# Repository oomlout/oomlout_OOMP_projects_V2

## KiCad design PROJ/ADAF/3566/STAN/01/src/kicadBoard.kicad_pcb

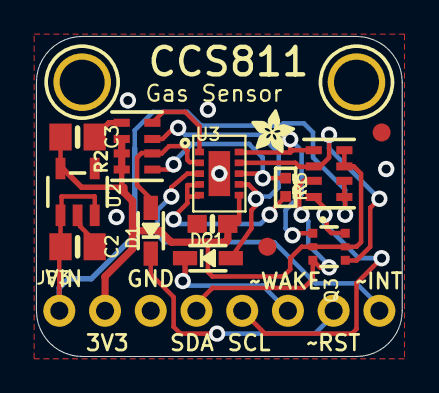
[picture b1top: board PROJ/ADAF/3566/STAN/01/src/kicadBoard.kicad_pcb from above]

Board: 2 copper layers, 20.3 x 17.8 mm, 18 parts (1 on the bottom side), 15 nets.

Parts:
C1: 0.1uF; 0603-NO
C2, C3: 10uF; 0805-NO
D1, D2: 1N4148; SOD-323
FID1, FID2: FIDUCIAL_1MM
JP3: 1X08_ROUND_70
Q3: 2N7002D; SOT363
R1: 10k; RESPACK_4X0603
R2: 100k; RESPACK_4X0603
R5: 10K NTC; _0402
U2: MIC5225-3.3; SOT23-5
U3: CCS811
U$1: ADAFRUIT_3.5MM
U$3, U$4: MOUNTINGHOLE2.5; MOUNTINGHOLE_2.5_PLATED
U$8: ADAFRUIT_2.5MM

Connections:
3.3V: C1.1, C3.1, JP3.2, Q3.2, Q3.5, R1.3, R1.4, R2.6, R2.7, R2.8, U2.5, U3.6
GND: C1.2, C2.2, C3.2, JP3.3, R2.5, U2.2, U3.THERMAL
unnamed: R5.2, U3.4, U3.5
unnamed: R2.1, R5.1, U3.8
unnamed: R2.4, U3.1
SCL: JP3.5, Q3.6, R1.8
SCL_3V: Q3.1, R1.5, U3.10
SDA: JP3.4, Q3.3, R1.7
SDA_3V: Q3.4, R1.6, U3.9
VIN: C2.1, JP3.1, R1.1, R1.2, U2.1, U2.3
~INT: JP3.8, U3.3
~RESET: D1.C, JP3.7
~RST_3V: D1.A, R2.2, U3.2
~WAKE_3V: D2.A, R2.3, U3.7
~WAKE: D2.C, JP3.6

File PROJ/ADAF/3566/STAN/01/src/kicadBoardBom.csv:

"Id";"Designator";"Package";"Quantity";"Designation";"Supplier and ref";
1;"Q3";"SOT363";1;"2N7002D";;;
2;"U$4,U$3";"MOUNTINGHOLE_2.5_PLATED";2;"MOUNTINGHOLE2.5";;;
3;"D1,D2";"SOD-323";2;"1N4148";;;
4;"C3,C2";"0805-NO";2;"10uF";;;
5;"R1";"RESPACK_4X0603";1;"10k";;;
6;"U2";"SOT23-5";1;"MIC5225-3.3";;;
7;"FID1,FID2";"FIDUCIAL_1MM";2;"FIDUCIAL_1MM";;;
8;"C1";"0603-NO";1;"0.1uF";;;
9;"R2";"RESPACK_4X0603";1;"100k";;;
10;"R5";"_0402";1;"10K NTC";;;
11;"U$8";"ADAFRUIT_2.5MM";1;"";;;
12;"JP3";"1X08_ROUND_70";1;"";;;
13;"U3";"CCS811";1;"CCS811";;;
14;"U$1";"ADAFRUIT_3.5MM";1;"";;;

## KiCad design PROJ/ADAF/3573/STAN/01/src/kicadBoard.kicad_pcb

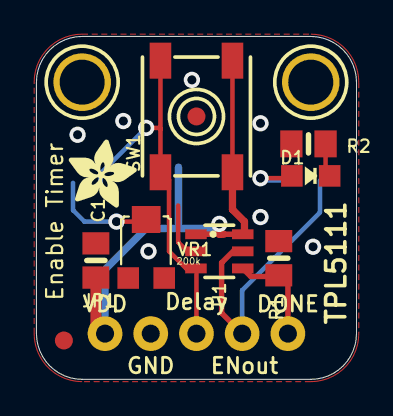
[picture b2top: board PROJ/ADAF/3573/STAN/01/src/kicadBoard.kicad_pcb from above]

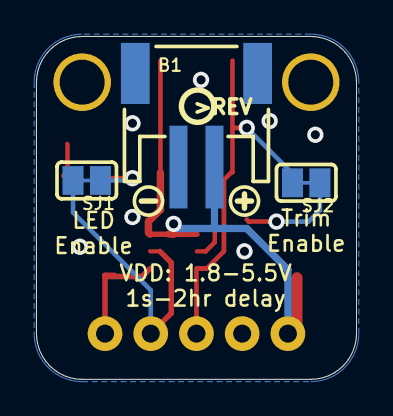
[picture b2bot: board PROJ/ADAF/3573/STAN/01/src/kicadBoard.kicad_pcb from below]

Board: 2 copper layers, 17.8 x 19.0 mm, 19 parts (6 on the bottom side), 8 nets.

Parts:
B1: JSTPH2
C1: 10uF; 0805-NO
D1: GREEN; CHIPLED_0805_NOOUTLINE
FID2, FID3: FIDUCIAL_1MM
JP1: 1X05_ROUND_76
R1: 1M; 0805-NO
R2: 1K; 0805-NO
SJ1, SJ2: SOLDERJUMPER_CLOSEDWIRE
SW1: MANUAL; EVQ-Q2_SMALLER
U1: TPL5111DDC; SOT23-6
U$8, U$9: MOUNTINGHOLE2.5; MOUNTINGHOLE_2.5_PLATED
U$10: ADAFRUIT_3.5MM
U$11: SYMBOL_PLUS
U$12: SYMBOL_MINUS
U$15: PCBFEAT-REV-040
VR1: 200k; TRIMPOT_BOURNS_TC33X-2

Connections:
DELAY: JP1.3, SJ2.2, SW1.B, SW1.B', U1.3
DONE: JP1.5, R1.2, U1.4
ENOUT: JP1.4, SJ1.2, U1.5
GND: B1.1, C1.2, JP1.2, R1.1, R2.1, U1.2, VR1.3
unnamed: SJ2.1, VR1.2
unnamed: D1.A, SJ1.1
unnamed: D1.C, R2.2
VDD: B1.2, C1.1, JP1.1, SW1.A, SW1.A', U1.1, U1.6

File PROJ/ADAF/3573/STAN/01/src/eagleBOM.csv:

"Part";"Value";"Device";"Package";"Description";"BOM";
"B1";"JSTPH2";"BATTERY";"JSTPH2";"CR1220 SMT - Digikey: 3001K-ND";"";
"C1";"10uF";"CAP_CERAMIC0805-NOOUTLINE";"0805-NO";"Ceramic Capacitors";"";
"D1";"GREEN";"LED0805_NOOUTLINE";"CHIPLED_0805_NOOUTLINE";"LED";"";
"FID2";"FIDUCIAL_1MM";"FIDUCIAL_1MM";"FIDUCIAL_1MM";"Fiducial Alignment Points";"EXCLUDE";
"FID3";"FIDUCIAL_1MM";"FIDUCIAL_1MM";"FIDUCIAL_1MM";"Fiducial Alignment Points";"EXCLUDE";
"JP1";"";"HEADER-1X576MIL";"1X05_ROUND_76";"PIN HEADER";"";
"R1";"1M";"RESISTOR0805_NOOUTLINE";"0805-NO";"Resistors";"";
"R2";"1K";"RESISTOR0805_NOOUTLINE";"0805-NO";"Resistors";"";
"SJ1";"";"SOLDERJUMPERCLOSED";"SOLDERJUMPER_CLOSEDWIRE";"SMD Solder JUMPER";"";
"SJ2";"";"SOLDERJUMPERCLOSED";"SOLDERJUMPER_CLOSEDWIRE";"SMD Solder JUMPER";"";
"SW1";"MANUAL";"SWITCH_TACT_SMT_EVQQ2_SMALL";"EVQ-Q2_SMALLER";"SMT Tact Switches";"";
"U$8";"MOUNTINGHOLE2.5";"MOUNTINGHOLE2.5";"MOUNTINGHOLE_2.5_PLATED";"Mounting Hole";"EXCLUDE";
"U$9";"MOUNTINGHOLE2.5";"MOUNTINGHOLE2.5";"MOUNTINGHOLE_2.5_PLATED";"Mounting Hole";"EXCLUDE";
"U1";"TPL5111DDC";"TPL5111";"SOT23-6";"TPL5111 Timer Based Power Gate";"";
"VR1";"200k";"TRIMPOTTC33X-2";"TRIMPOT_BOURNS_TC33X-2";"3-Pin SMT Trimpots";"";

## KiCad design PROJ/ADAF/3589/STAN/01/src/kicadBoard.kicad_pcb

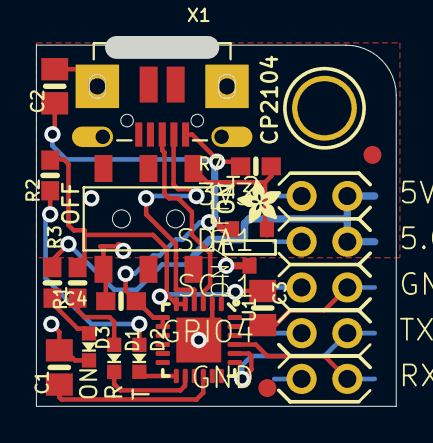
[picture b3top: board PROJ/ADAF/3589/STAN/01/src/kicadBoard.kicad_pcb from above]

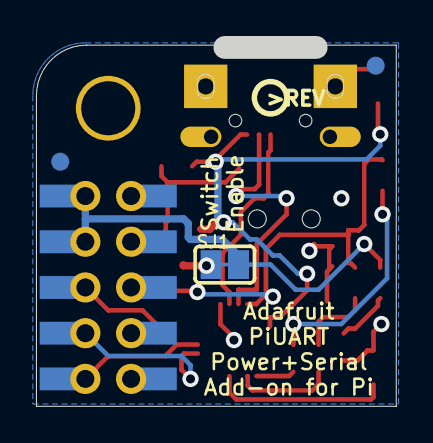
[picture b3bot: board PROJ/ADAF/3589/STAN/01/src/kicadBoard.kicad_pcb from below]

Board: 2 copper layers, 20.0 x 20.1 mm, 24 parts (4 on the bottom side), 20 nets.

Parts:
C1, C2, C3: 10uF; 0805-NO
C4: 0.1uF; 0603-NO
D1: RED; CHIPLED_0603_NOOUTLINE
D2: YELLOW; CHIPLED_0603_NOOUTLINE
D3: GREEN; CHIPLED_0603_NOOUTLINE
FID1, FID2, FID3, FID4: FIDUCIAL_1MM
ON/OFF0: EG1390
R1, R2: 2.2K; 0603-NO
R3, R7: 10K; 0603-NO
SJ1: SOLDERJUMPER_CLOSEDWIRE
T2: DMG3415U; SOT-23
U1: CP2104; QFN24_4MM_SMSC
U$8: ADAFRUIT_2.5MM
U$9: RASPBERRYPI_2X5; RASPBERRYPI_2X5_THMSMT
U$17: PCBFEAT-REV-040
U$18: MOUNTINGHOLE3.0THIN; MOUNTINGHOLE_3.0_PLATEDTHIN
X1: 20329; 4UCONN_20329_V2

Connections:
3.3V: C3.1, R1.2, R2.2, U1.5, U1.6
GND: C1.2, C2.2, C3.2, C4.2, D3.C, ON/OFF0.P2, ON/OFF0.S1, U1.2, U1.THERM, U$9.6, U$9.6', U$9.9, U$9.9', X1.BASE@1, X1.BASE@2, X1.GND, X1.SPRT@1, X1.SPRT@2, X1.SPRT@3, X1.SPRT@4
unnamed: D1.A, R1.1
unnamed: U1.3, X1.D+
unnamed: U1.4, X1.D-
unnamed: C1.1, U1.16
unnamed: D2.A, R2.1
unnamed: D1.C, U1.14
unnamed: D2.C, U1.13
unnamed: U$9.1, U$9.1'
unnamed: U$9.3, U$9.3'
unnamed: U$9.7, U$9.7'
unnamed: U$9.5, U$9.5'
unnamed: R3.2, SJ1.2, U$9.2, U$9.2', U$9.4, U$9.4'
unnamed: ON/OFF0.O2, R7.1, T2.3
unnamed: D3.A, R3.1
RXD: U1.21, U$9.10, U$9.10'
TXD: U1.20, U$9.8, U$9.8'
VBUS: C2.1, C4.1, R7.2, T2.2, U1.7, U1.8, X1.VBUS
VIN: SJ1.1, T2.1

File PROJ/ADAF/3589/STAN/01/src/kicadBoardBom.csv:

"Id";"Designator";"Package";"Quantity";"Designation";"Supplier and ref";
1;"U1";"QFN24_4MM_SMSC";1;"CP2104";;;
2;"FID2,FID1,FID3,FID4";"FIDUCIAL_1MM";4;"FIDUCIAL_1MM";;;
3;"R7,R3";"0603-NO";2;"10K";;;
4;"D3";"CHIPLED_0603_NOOUTLINE";1;"GREEN";;;
5;"C4";"0603-NO";1;"0.1uF";;;
6;"U$18";"MOUNTINGHOLE_3.0_PLATEDTHIN";1;"MOUNTINGHOLE3.0THIN";;;
7;"U$9";"RASPBERRYPI_2X5_THMSMT";1;"RASPBERRYPI_2X5";;;
8;"C1,C3,C2";"0805-NO";3;"10uF";;;
9;"ON/OFF0";"EG1390";1;"EG1390";;;
10;"X1";"4UCONN_20329_V2";1;"20329";;;
11;"R1,R2";"0603-NO";2;"2.2K";;;
12;"D2";"CHIPLED_0603_NOOUTLINE";1;"YELLOW";;;
13;"D1";"CHIPLED_0603_NOOUTLINE";1;"RED";;;
14;"U$8";"ADAFRUIT_2.5MM";1;"";;;
15;"T2";"SOT-23";1;"DMG3415U";;;
16;"SJ1";"SOLDERJUMPER_CLOSEDWIRE";1;"";;;
17;"U$17";"PCBFEAT-REV-040";1;"";;;

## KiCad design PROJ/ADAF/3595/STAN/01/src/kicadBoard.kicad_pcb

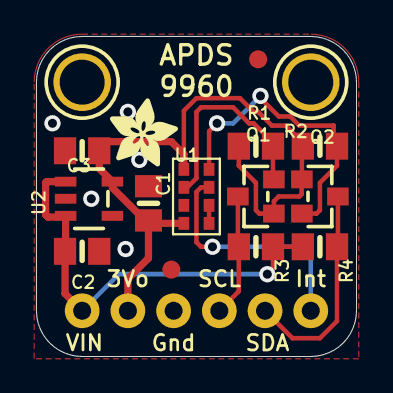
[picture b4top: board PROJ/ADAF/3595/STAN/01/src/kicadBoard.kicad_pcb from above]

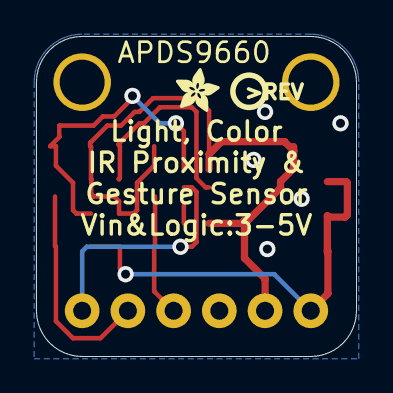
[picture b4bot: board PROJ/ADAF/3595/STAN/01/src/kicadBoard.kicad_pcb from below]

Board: 2 copper layers, 17.8 x 17.8 mm, 19 parts (2 on the bottom side), 9 nets.

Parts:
C1: 0.1uF; 0805-NO
C2, C3: 10uF; 0805-NO
FID1, FID2: FIDUCIAL_1MM
JP1: 1X06_ROUND_76
Q1, Q2: BSS138; SOT23-WIDE
R1, R2, R3, R4: 10K; 0805-NO
U1: APDS-9960
U2: SOT23-5
U$1, U$2: MOUNTINGHOLE2.5; MOUNTINGHOLE_2.5_PLATED
U$17: PCBFEAT-REV-040
U$18: ADAFRUIT_2.5MM
U$19: ADAFRUIT_3.5MM

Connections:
3.3V: C1.1, C3.1, JP1.2, Q1.1, Q2.1, R1.2, R2.2, U1.5, U1.8, U2.5
GND: C1.2, C2.2, C3.2, JP1.3, U1.6, U2.2
INT: JP1.6, U1.2
unnamed: U1.3, U1.4
SCL: JP1.4, Q1.3, R3.1
SCL_3V: Q1.2, R1.1, U1.7
SDA: JP1.5, Q2.3, R4.1
SDA_3V: Q2.2, R2.1, U1.1
VIN: C2.1, JP1.1, R3.2, R4.2, U2.1, U2.3

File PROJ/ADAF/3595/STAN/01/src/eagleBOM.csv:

"Part";"Value";"Device";"Package";"Description";"BOM";
"C1";"0.1uF";"CAP_CERAMIC0805-NOOUTLINE";"0805-NO";"Ceramic Capacitors";"";
"C2";"10uF";"CAP_CERAMIC0805-NOOUTLINE";"0805-NO";"Ceramic Capacitors";"";
"C3";"10uF";"CAP_CERAMIC0805-NOOUTLINE";"0805-NO";"Ceramic Capacitors";"";
"FID1";"FIDUCIAL_1MM";"FIDUCIAL_1MM";"FIDUCIAL_1MM";"Fiducial Alignment Points";"EXCLUDE";
"FID2";"FIDUCIAL_1MM";"FIDUCIAL_1MM";"FIDUCIAL_1MM";"Fiducial Alignment Points";"EXCLUDE";
"JP1";"";"HEADER-1X676MIL";"1X06_ROUND_76";"PIN HEADER";"";
"Q1";"BSS138";"MOSFET-NWIDE";"SOT23-WIDE";"N-Channel Mosfet";"";
"Q2";"BSS138";"MOSFET-NWIDE";"SOT23-WIDE";"N-Channel Mosfet";"";
"R1";"10K";"RESISTOR0805_NOOUTLINE";"0805-NO";"Resistors";"";
"R2";"10K";"RESISTOR0805_NOOUTLINE";"0805-NO";"Resistors";"";
"R3";"10K";"RESISTOR0805_NOOUTLINE";"0805-NO";"Resistors";"";
"R4";"10K";"RESISTOR0805_NOOUTLINE";"0805-NO";"Resistors";"";
"U$1";"MOUNTINGHOLE2.5";"MOUNTINGHOLE2.5";"MOUNTINGHOLE_2.5_PLATED";"Mounting Hole";"EXCLUDE";
"U$2";"MOUNTINGHOLE2.5";"MOUNTINGHOLE2.5";"MOUNTINGHOLE_2.5_PLATED";"Mounting Hole";"EXCLUDE";
"U1";"APDS-9960";"APDS-9960";"APDS-9960";"APDS-9960 - Digital Proximity Sensor with Ambient Light/RGB/Gesture Detection";"";
"U2";"";"VREG_SOT23-5";"SOT23-5";"SOT23-5 Fixed Voltage Regulators";"";

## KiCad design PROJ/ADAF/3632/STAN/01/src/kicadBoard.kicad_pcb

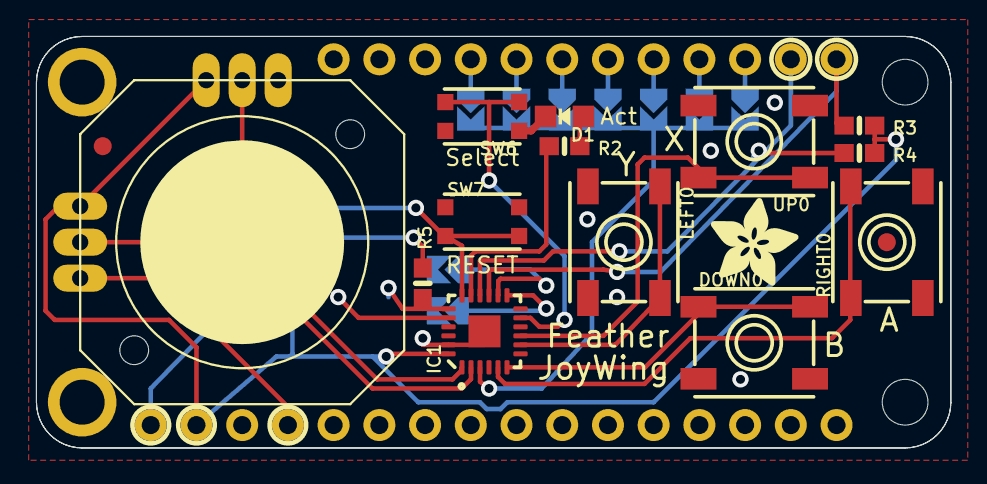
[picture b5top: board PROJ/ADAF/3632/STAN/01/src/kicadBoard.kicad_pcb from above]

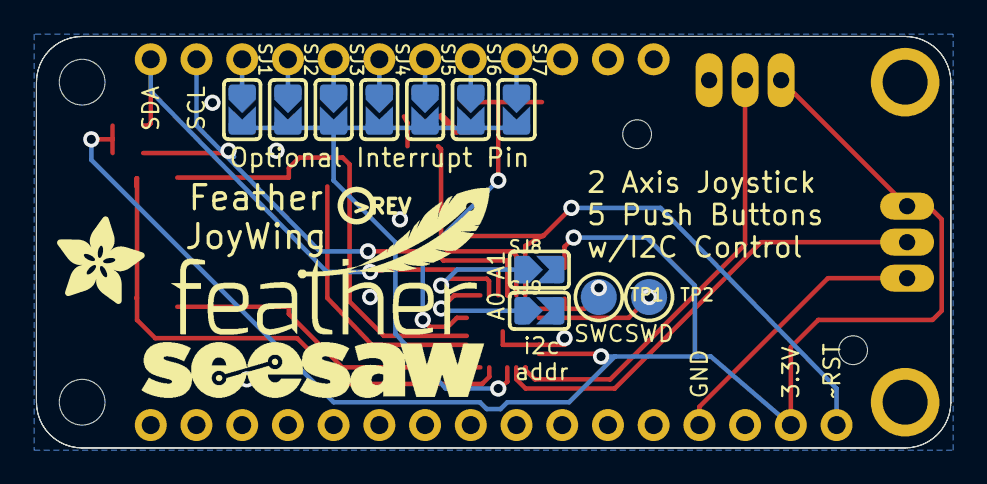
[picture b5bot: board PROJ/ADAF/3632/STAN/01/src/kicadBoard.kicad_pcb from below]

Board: 16 copper layers, 50.8 x 22.9 mm, 32 parts (15 on the bottom side), 26 nets.

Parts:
D1: RED; CHIPLED_0805_NOOUTLINE
DOWN0: 6mm; EVQ-Q2_SMALLER
FID1, FID2: FIDUCIAL_1MM
IC1: ATSAMD09D14A-MU; QFN24_4MM
JOY1: JOYSTICK_ANALOG_XY; JOYSTICK_ANALOG_MINITHM
LEFT0: 6mm; EVQ-Q2_SMALLER
MS1: FEATHERWING
R2, R5: 1k; 0603-NO
R3: 10K; 0603-NO
R4: 10k; 0603-NO
RIGHT0: 6mm; EVQ-Q2_SMALLER
SJ1, SJ2, SJ3, SJ4, SJ5, SJ6, SJ7, SJ8, SJ9: SOLDERJUMPER_ARROW_NOPASTE
SW6, SW7: KMR2; BTN_KMR2_4.6X2.8
TP1, TP2: TESTPOINT_ROUND_2MM
U$7: PCBFEAT-REV-040
U$9, U$11: ADAFRUIT_5MM
U$10: FEATHERLOGO_MED
U$12: SEESAW_LOGO
UP0: 6mm; EVQ-Q2_SMALLER

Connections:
3.3V: IC1.24, JOY1.X+, JOY1.Y+, MS1.2, R3.2, R4.2, R5.2
GND: D1.C, DOWN0.A, DOWN0.A', IC1.23, IC1.THERM, JOY1.X-, JOY1.Y-, LEFT0.A, LEFT0.A', MS1.4, RIGHT0.A, RIGHT0.A', SJ8.2, SJ9.2, SW6.A, SW6.A', SW7.A, SW7.A', UP0.A, UP0.A'
unnamed: MS1.19, SJ1.1
unnamed: MS1.20, SJ2.1
unnamed: MS1.21, SJ3.1
unnamed: MS1.22, SJ4.1
unnamed: IC1.17, R2.1
unnamed: MS1.23, SJ5.1
unnamed: MS1.24, SJ6.1
unnamed: MS1.25, SJ7.1
unnamed: D1.A, R2.2
PA02_A0: IC1.1, JOY1.Y
PA03_A1: IC1.2, JOY1.X
PA04_A2: IC1.3, SJ1.2, SJ2.2, SJ3.2, SJ4.2, SJ5.2, SJ6.2, SJ7.2
PA06_A4: IC1.5, RIGHT0.B, RIGHT0.B'
PA07_A5: DOWN0.B, DOWN0.B', IC1.6
PA09_XOSC: IC1.8, LEFT0.B, LEFT0.B'
PA10_A18: IC1.9, UP0.B, UP0.B'
PA14: IC1.11, SW6.B, SW6.B'
PA16_D16: IC1.13, SJ9.1
PA17_D17: IC1.14, SJ8.1
PA22_SDA: IC1.15, MS1.17, R3.1
PA23_SCL: IC1.16, MS1.18, R4.1
SWCLK: IC1.19, R5.1, TP1.P$1
SWDIO: IC1.20, TP2.P$1
~RESET: IC1.18, MS1.1, SW7.B, SW7.B'

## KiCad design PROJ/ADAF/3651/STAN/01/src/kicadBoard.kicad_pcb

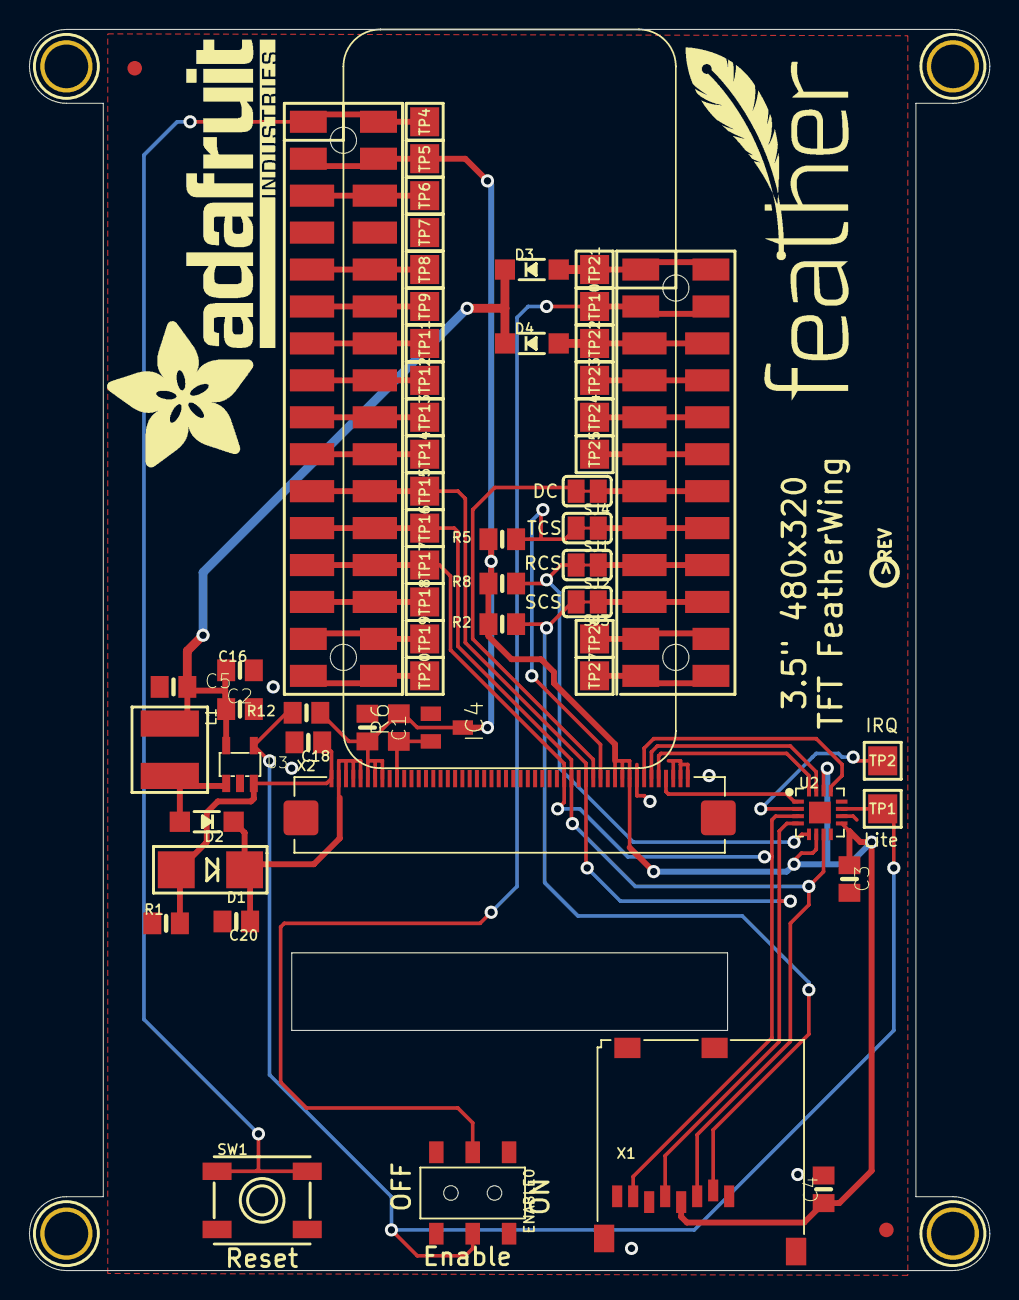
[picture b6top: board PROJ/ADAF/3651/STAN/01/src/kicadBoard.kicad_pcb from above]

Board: 16 copper layers, 66.0 x 85.3 mm, 66 parts (1 on the bottom side), 43 nets.

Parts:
C1, C16, C20: 1uF; 0805-NO
C2, C3, C4, C5: 10uF; 0805-NO
C18: 0.1uF; 0805-NO
D1: MM3Z24VT1G; SMADIODE
D2: MBR0540; SOD-123
D3, D4: MBR120; SOD-123
ENABLE0: Slide Switch; EG1390
IC4: APX803-SAG; SOT23
L1: 15uH; INDUCTOR_5X5MM_NR5040_NOTHERMALS
MS2: FEATHERWING_SMTDUAL; FEATHERWING_SMT2
R1: 12Ω; 0805-NO
R2, R5, R8: 100K; 0805-NO
R6: 10K; R0805
R12: 10K; 0805-NO
SJ1, SJ2, SJ3, SJ4: SOLDERJUMPER_CLOSEDWIRE
SW1: EVQQ2; EVQ-Q2_SMALLER
TP1, TP2, TP4, TP5, TP6, TP7, TP8, TP9, TP10, TP11, TP12, TP13, TP14, TP15, TP16, TP17, TP18, TP19, TP20, TP21, TP22, TP23, TP24, TP25, TP26, TP27: TESTPOINT_PAD_2MM
U2: STMPE811; QFN16_3MM
U3: FAN5333BSX; SOT23-5@1
U$7, U$15, U$16, U$17: MOUNTINGHOLE3.0THIN; MOUNTINGHOLE_3.0_PLATEDTHIN
U$9, U$23: FIDUCIAL_1MM
U$11: FEATHERLOGO
U$19: ADAFRUIT_TEXT_30MM
U$37: PCBFEAT-REV-040
X1: MicroSD; MICROSD
X2: 3.5" TFT; TFT_3.5IN_320X480_50PIN

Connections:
3.3V: C1.1, C3.1, C4.1, IC4.3, MS2.2, MS2.2', R2.2, R5.2, R6.2, R8.2, R12.1, TP5.P$1, U2.6, U2.9, U2.14, X1.4, X2.6, X2.7, X2.8, X2.40, X2.41, X2.42
+5V: C2.1, C5.1, C16.1, D3.C, D4.C, L1.P$1, U3.5
+24V: C20.1, D1.C, D2.C, X2.2, X2.3, X2.4, X2.5
A: MS2.5, MS2.5', TP8.P$1
AREF: MS2.3, MS2.3', TP6.P$1
B: MS2.6, MS2.6', TP9.P$1
C: MS2.7, MS2.7', TP11.P$1
D: MS2.8, MS2.8', TP12.P$1
E: MS2.9, MS2.9', TP13.P$1
EN: ENABLE0.P2, MS2.27, MS2.27', TP10.P$1
F: MS2.10, MS2.10', TP14.P$1
G: MS2.16, MS2.16', TP20.P$1
GND: C1.2, C2.2, C3.2, C4.2, C5.2, C16.2, C18.2, C20.2, ENABLE0.S1, ENABLE0.S2, IC4.1, MS2.4, MS2.4', R1.1, SW1.A, SW1.A', TP7.P$1, U2.10, U3.2, X1.6, X1.MT1, X1.MT2, X2.43, X2.48, X2.49, X2.50
H: MS2.19, MS2.19', SJ3.1
I: MS2.20, MS2.20', SJ2.1
J: MS2.21, MS2.21', SJ1.1
K: MS2.22, MS2.22', SJ4.1
L: MS2.23, MS2.23', TP25.P$1
LCD_LITE: ENABLE0.P1, R12.2, TP1.P$1, U2.11, U3.4
LEDK: C18.1, D1.A, R1.2, U3.3, X2.1
M: MS2.24, MS2.24', TP24.P$1
MISO: MS2.13, MS2.13', TP17.P$1, U2.3, X1.7, X2.33
MOSI: MS2.12, MS2.12', TP16.P$1, U2.7, X1.3, X2.34
N: MS2.25, MS2.25', TP23.P$1
unnamed: D2.A, L1.P$2, U3.1
RT_CS: R8.1, SJ2.2, U2.5
RT_INT: TP2.P$1, U2.2
RX: MS2.14, MS2.14', TP18.P$1
SCL: MS2.18, MS2.18', TP26.P$1
SCLK: MS2.11, MS2.11', TP15.P$1, U2.4, X1.5, X2.36
SDA: MS2.17, MS2.17', TP27.P$1
SD_CS: R2.1, SJ3.2, X1.2
TFT_CS: R5.1, SJ1.2, X2.38
TFT_DC: SJ4.2, X2.37
TX: MS2.15, MS2.15', TP19.P$1
USB: D4.A, MS2.26, MS2.26', TP22.P$1
VBAT: D3.A, MS2.28, MS2.28', TP21.P$1
XL: U2.16, X2.46
XR: U2.13, X2.44
YD: U2.15, X2.45
YU: U2.1, X2.47
~RESET: MS2.1, MS2.1', SW1.B, SW1.B', TP4.P$1
~TFT_RST: IC4.2, R6.1, X2.10

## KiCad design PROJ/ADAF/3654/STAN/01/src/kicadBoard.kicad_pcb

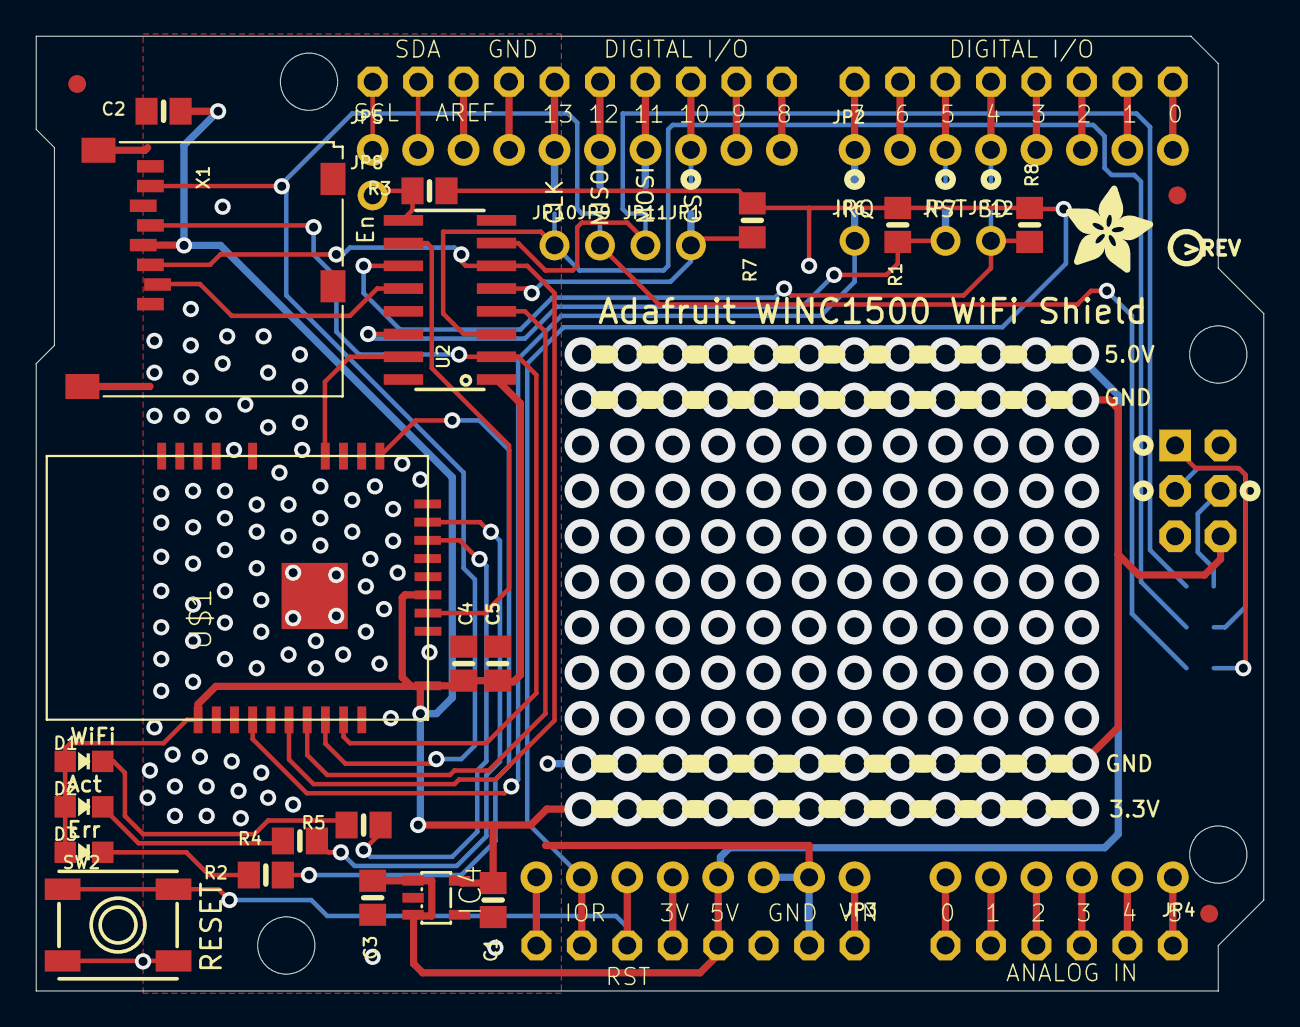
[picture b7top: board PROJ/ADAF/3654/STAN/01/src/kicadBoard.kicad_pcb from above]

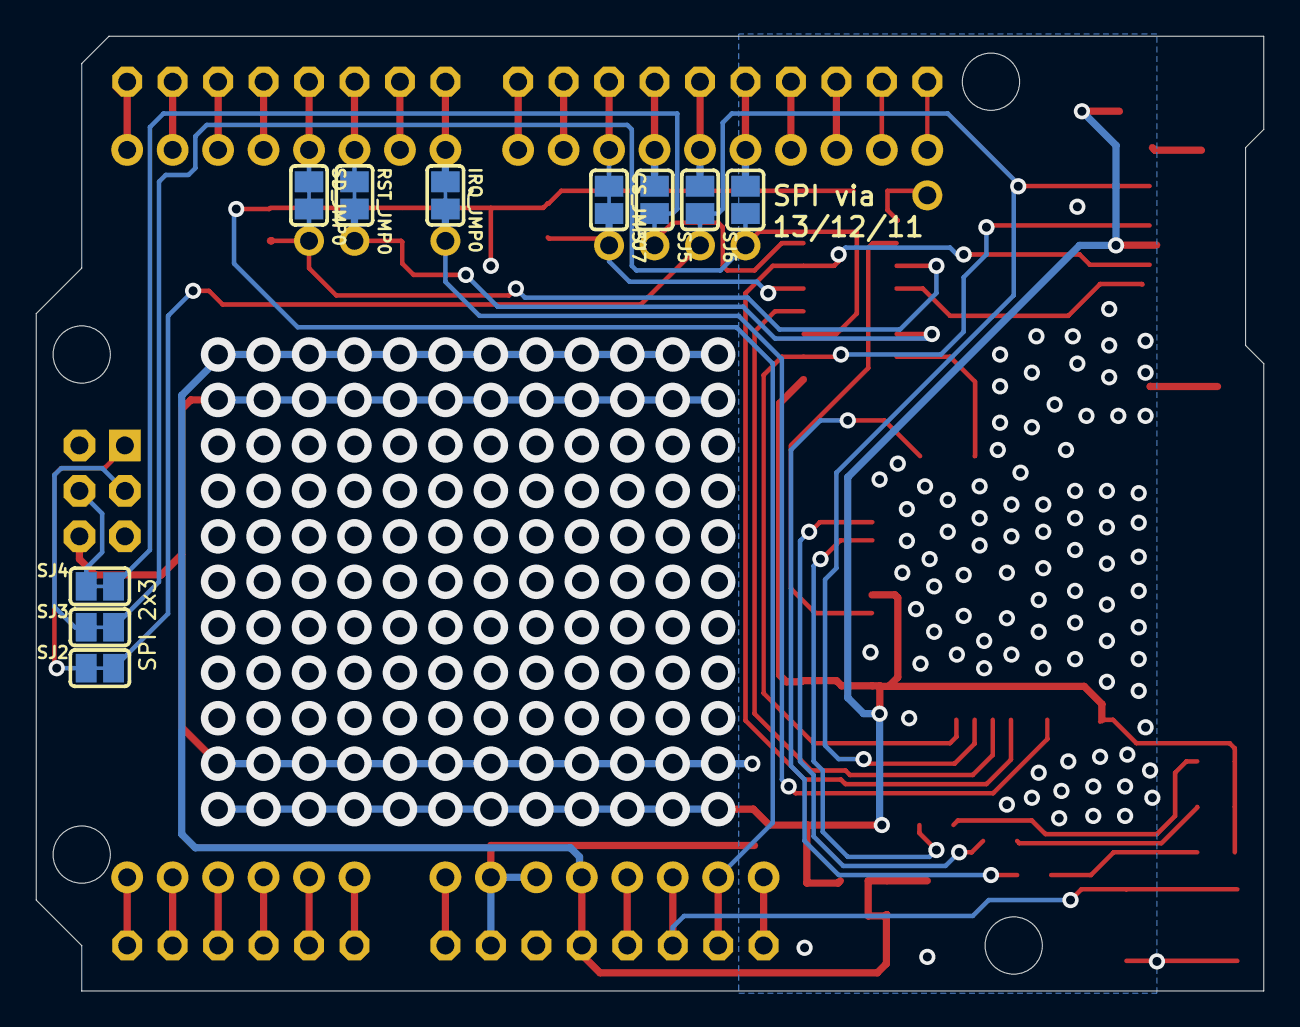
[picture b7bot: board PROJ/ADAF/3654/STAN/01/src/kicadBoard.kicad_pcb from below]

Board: 2 copper layers, 68.6 x 53.3 mm, 52 parts (10 on the bottom side), 54 nets.

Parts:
@HOLE0, @HOLE1, @HOLE2, @HOLE3: (no value)
C1, C2, C3, C4: 10uF; 0805-NO
C5: 1uF; 0805-NO
CS_JMP0: SOLDERJUMPER_CLOSEDWIRE
D1: green; CHIPLED_0805_NOOUTLINE
D2: Yellow; CHIPLED_0805_NOOUTLINE
D3: Red; CHIPLED_0805_NOOUTLINE
FID1, FID2, FID3: FIDUCIAL_1MM
IC4: AP2112-3.3; SOT23-5L
IRQ_JMP0: SOLDERJUMPER_CLOSEDWIRE
JP1, JP6, JP7, JP8, JP9, JP10, JP11, JP12: 1X01_ROUND
JP2, JP3: 1X08_ROUND_70
JP4: 1X06_ROUND_70
JP5: 1X10_ROUND70
M1: ARDUINO_R3_ICSP_NODIM; ARDUINOR3_ICSP_NODIM
R1, R3, R7, R8: 100K; 0805-NO
R2, R4, R5: 1K; 0805-NO
RST_JMP0: SOLDERJUMPER_CLOSEDWIRE
SD_JMP0: SOLDERJUMPER_CLOSEDWIRE
SJ2: ICSP_MISO; SOLDERJUMPER_CLOSEDWIRE
SJ3: ISCP_SCLK; SOLDERJUMPER_CLOSEDWIRE
SJ4: ICSP_MOSI; SOLDERJUMPER_CLOSEDWIRE
SJ5: D12_MISO; SOLDERJUMPER_REFLOW_NOPASTE
SJ6: D13_SCLK; SOLDERJUMPER_REFLOW_NOPASTE
SJ7: D11_MOSI; SOLDERJUMPER_REFLOW_NOPASTE
SW2: Tactile; EVQ-Q2_SMALLER
U2: 74HC4050; SOIC16
U$1: ATWINC1500_MR210PB; ATWINC1500_MR210PA
U$9: ADAFRUIT_5MM
U$21: PCBFEAT-REV-040
X1: microSd; MICROSD

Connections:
3.3V: C1.1, C2.1, C4.1, C5.1, D1.A, D2.A, D3.A, IC4.5, U2.1, U$1.J10, U$1.J20, U$1.J23, X1.4
+3V: JP3.5, M1.3V
+5V: C3.1, IC4.1, IC4.3, JP3.4, M1.5V
A0: JP4.6, M1.A0
A1: JP4.5, M1.A1
A2: JP4.4, M1.A2
A3: JP4.3, M1.A3
A4: JP4.2, M1.A4
A5: JP4.1, M1.A5
AREF: JP5.3, M1.AREF
CS_3V: U2.4, U$1.J16
D0: JP2.8, M1.D0
D1: JP2.7, M1.D1
D2: JP2.6, M1.D2
D3: JP2.5, M1.D3
D4: JP2.4, M1.D4, SD_JMP0.1
D5: JP2.3, M1.D5, RST_JMP0.1
D6: JP2.2, M1.D6
D7: IRQ_JMP0.1, JP2.1, M1.D7
D8: JP5.10, M1.D8
D9: JP5.9, M1.D9
D10: CS_JMP0.1, JP5.8, M1.D10
D11: JP5.7, M1.D11, SJ7.2
D12: JP5.6, M1.D12, SJ5.2
D13: JP5.5, M1.D13, SJ6.2
EN_3V: U2.10, U$1.J22
GND: C1.2, C2.2, C3.2, C4.2, C5.2, IC4.2, JP3.2, JP3.3, JP5.4, M1.GND, M1.GND@1, M1.GND@3, SW2.A, SW2.A', U2.8, U$1.J9, U$1.J12, U$1.J28, U$1.MTGND, X1.6, X1.MT1, X1.MT2
GPIO15: R5.1, U$1.J26
GPIO16: R4.1, U$1.J27
MISO: JP9.1, SJ2.2, SJ5.1, U$1.J17, X1.7
MISO_ICSP: M1.MISO, SJ2.1
MOSI: JP11.1, SJ4.2, SJ7.1, U2.7
MOSI_3V: U2.6, U$1.J15, X1.3
MOSI_ICSP: M1.MOSI, SJ4.1
unnamed: D3.C, R2.2
unnamed: D2.C, R4.2
unnamed: D1.C, R5.2
unnamed: R2.1, U$1.J1
NC: JP3.8, M1.RESERVED
RESET: JP3.6, M1.RESET, SW2.B, SW2.B'
RST_3V: U2.15, U$1.J4
SCK: JP10.1, SJ3.2, SJ6.1, U2.3
SCK_3V: U2.2, U$1.J18, X1.5
SCK_ICSP: M1.SCK, SJ3.1
SCL: JP5.1, M1.SCL
SDA: JP5.2, M1.SDA
SDCS: JP12.1, R8.1, SD_JMP0.2, U2.11
SDCS_3V: U2.12, X1.2
VIN: JP3.1, M1.VIN
VIOREF: JP3.7, M1.IOREF, R1.1, R3.1, R7.1, R8.2
WINC_CS: CS_JMP0.2, JP1.1, R7.2, U2.5
WINC_EN: JP8.1, R3.2, U2.9
WINC_IRQ: IRQ_JMP0.2, JP6.1, U$1.J13
WINC_RST: JP7.1, R1.2, RST_JMP0.2, U2.14

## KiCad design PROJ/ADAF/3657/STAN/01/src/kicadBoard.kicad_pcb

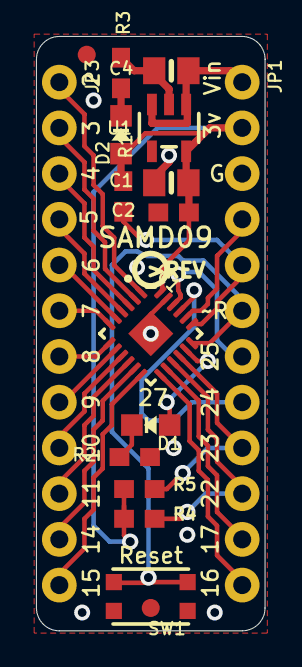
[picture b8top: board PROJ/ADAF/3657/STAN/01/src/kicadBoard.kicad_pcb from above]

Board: 2 copper layers, 12.7 x 33.0 mm, 19 parts (1 on the bottom side), 27 nets.

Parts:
C1, C4: 10uF; 0805-NO
C2: 0.1uF; 0603-NO
D1: RED; CHIPLED_0805_NOOUTLINE
D2: GREEN; CHIPLED_0805_NOOUTLINE
FID1, FID2: FIDUCIAL""; FIDUCIAL_1MM
IC1: ATSAMD09D14A-MU; QFN24_4MM
JP1, JP3: 1X12_ROUND_76MIL
R1, R2, R3: 1K; 0603-NO
R4, R5: 10k; 0603-NO
SW1: KMR2; BTN_KMR2_4.6X2.8
U1: AP2112K; SOT23-5
U$7: SEESAW_LOGO
U$12: PCBFEAT-REV-040

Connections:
3.3V: C1.1, C2.1, D2.A, IC1.24, JP1.2, R1.2, R4.1, R5.1, U1.5
+5V: C4.1, JP1.1, U1.1, U1.3
GND: C1.2, C2.2, C4.2, IC1.23, IC1.THERM, JP1.3, R2.1, R3.2, SW1.A, SW1.A', U1.2
unnamed: D1.C, R2.2
unnamed: D2.C, R3.1
PA02: IC1.1, JP3.1
PA03: IC1.2, JP3.2
PA04: IC1.3, JP3.3
PA05: IC1.4, JP3.4
PA06: IC1.5, JP3.5
PA07: IC1.6, JP3.6
PA08: IC1.7, JP3.7
PA09: IC1.8, JP3.8
PA10: IC1.9, JP3.9
PA11: IC1.10, JP3.10
PA14: IC1.11, JP3.11
PA15: IC1.12, JP3.12
PA16: IC1.13, JP1.12
PA17: IC1.14, JP1.11
PA22: IC1.15, JP1.10, R4.2
PA23: IC1.16, JP1.9, R5.2
PA24: IC1.21, JP1.8
PA25: IC1.22, JP1.7
PA27: D1.A, IC1.17
SWCLK: IC1.19, JP1.5, R1.1
SWDIO: IC1.20, JP1.4
~RESET: IC1.18, JP1.6, SW1.B, SW1.B'
